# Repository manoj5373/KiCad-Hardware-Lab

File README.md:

# KiCad-Hardware-Lab
A collection of practical electronics and PCB design experiments developed using KiCad, covering analog circuits, digital logic, power supplies, counters, amplifiers, and hardware design.

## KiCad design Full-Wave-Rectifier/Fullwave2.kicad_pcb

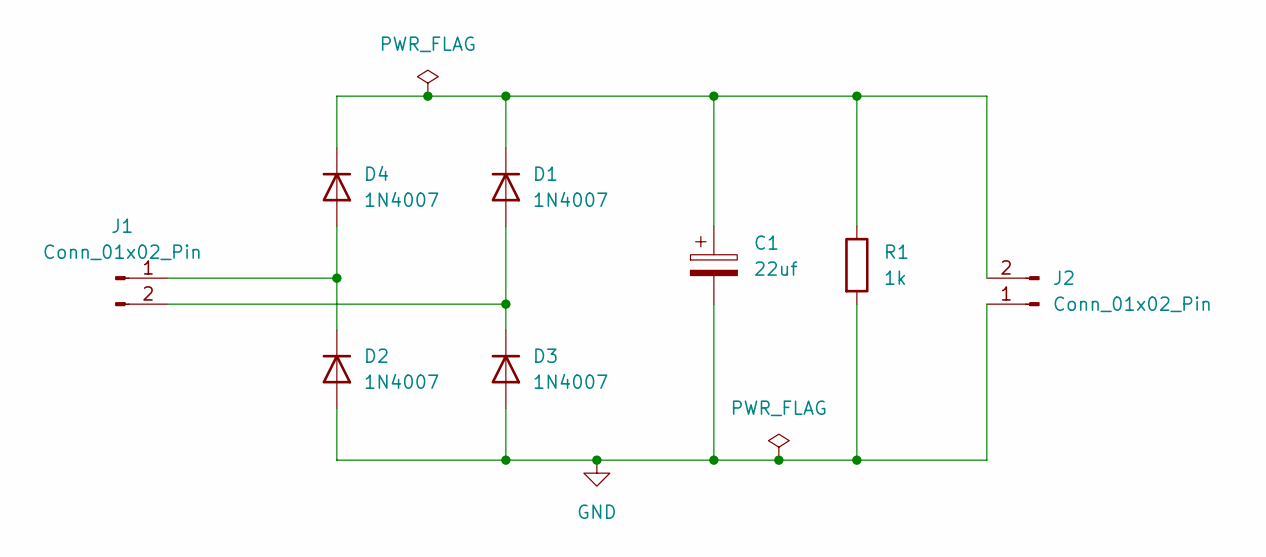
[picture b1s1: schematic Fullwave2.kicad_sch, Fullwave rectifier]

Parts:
C1: 22uf; CP_Radial_D6.3mm_P2.50mm
D1, D2, D3, D4: 1N4007; D_DO-41_SOD81_P10.16mm_Horizontal
J1, J2: Conn_01x02_Pin; PinHeader_1x02_P2.54mm_Vertical
R1: 1k; R_Axial_DIN0207_L6.3mm_D2.5mm_P10.16mm_Horizontal

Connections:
GND: C1.2, D2.2 (A), D3.2 (A), J2.1, R1.2
unnamed: D1.2 (A), D3.1 (K), J1.2
unnamed: C1.1, D1.1 (K), D4.1 (K), J2.2, R1.1
unnamed: D2.1 (K), D4.2 (A), J1.1

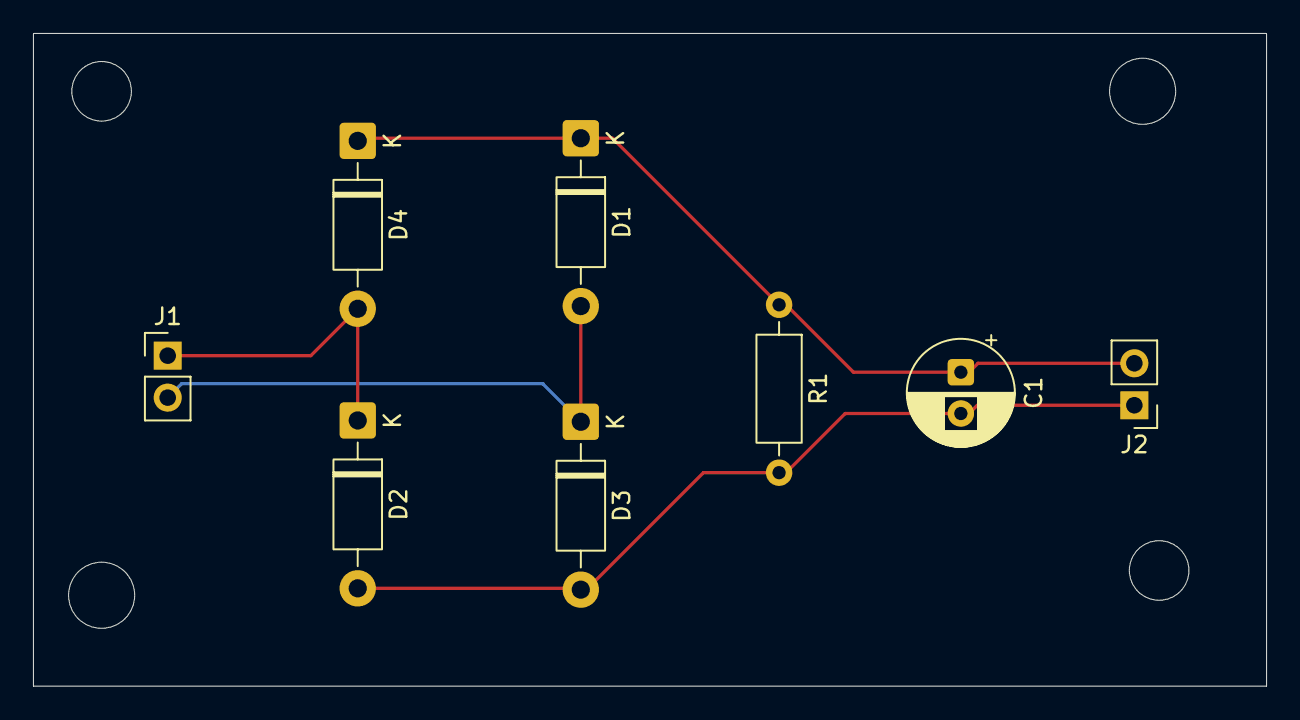
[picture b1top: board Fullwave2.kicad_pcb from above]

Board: 2 copper layers, 74.6 x 39.5 mm, 8 parts (0 on the bottom side), 4 nets.

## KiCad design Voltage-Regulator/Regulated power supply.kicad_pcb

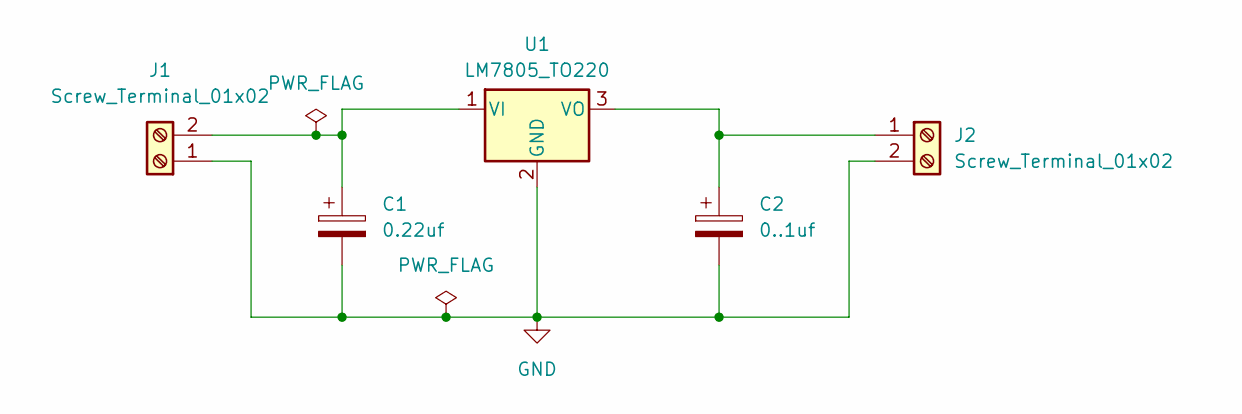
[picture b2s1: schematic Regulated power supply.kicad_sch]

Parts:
C1: 0.22uf; CP_Radial_D5.0mm_P2.50mm
C2: 0..1uf; CP_Radial_D5.0mm_P2.50mm
J1, J2: Screw_Terminal_01x02; TerminalBlock_Phoenix_PT-1,5-2-3.5-H_1x02_P3.50mm_Horizontal
U1: LM7805_TO220; TO-220-3_Vertical

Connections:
GND: C1.2, C2.2, J1.1, J2.2, U1.2 (GND)
unnamed: C1.1, J1.2, U1.1 (VI)
unnamed: C2.1, J2.1, U1.3 (VO)

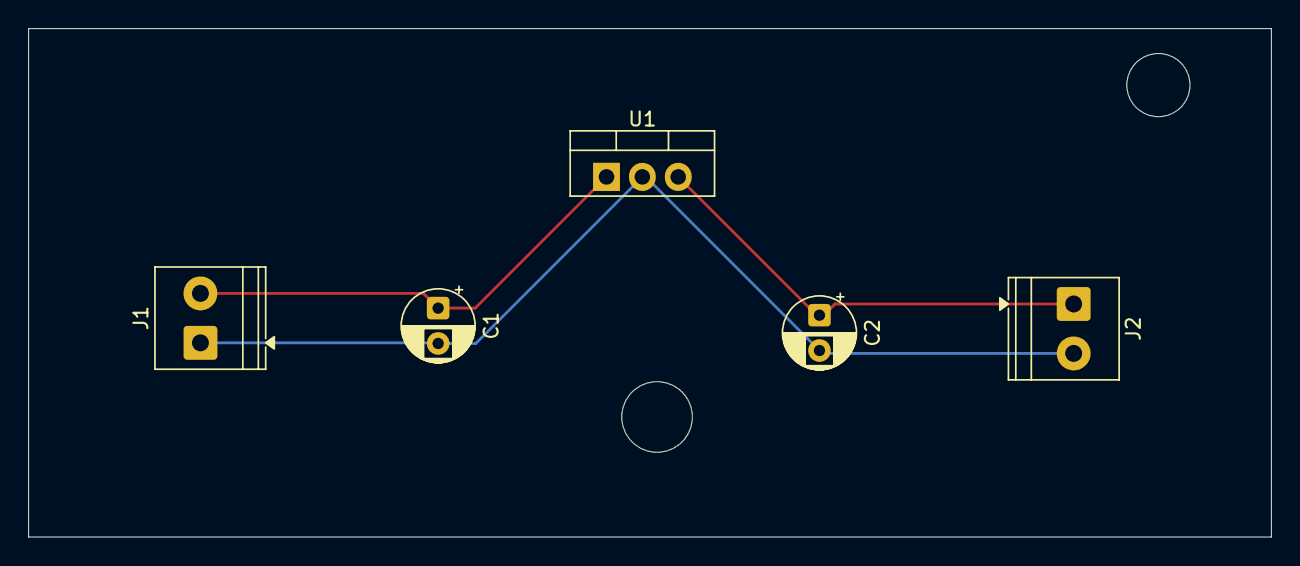
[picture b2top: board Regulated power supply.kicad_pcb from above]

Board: 2 copper layers, 88.0 x 36.0 mm, 5 parts (0 on the bottom side), 3 nets.

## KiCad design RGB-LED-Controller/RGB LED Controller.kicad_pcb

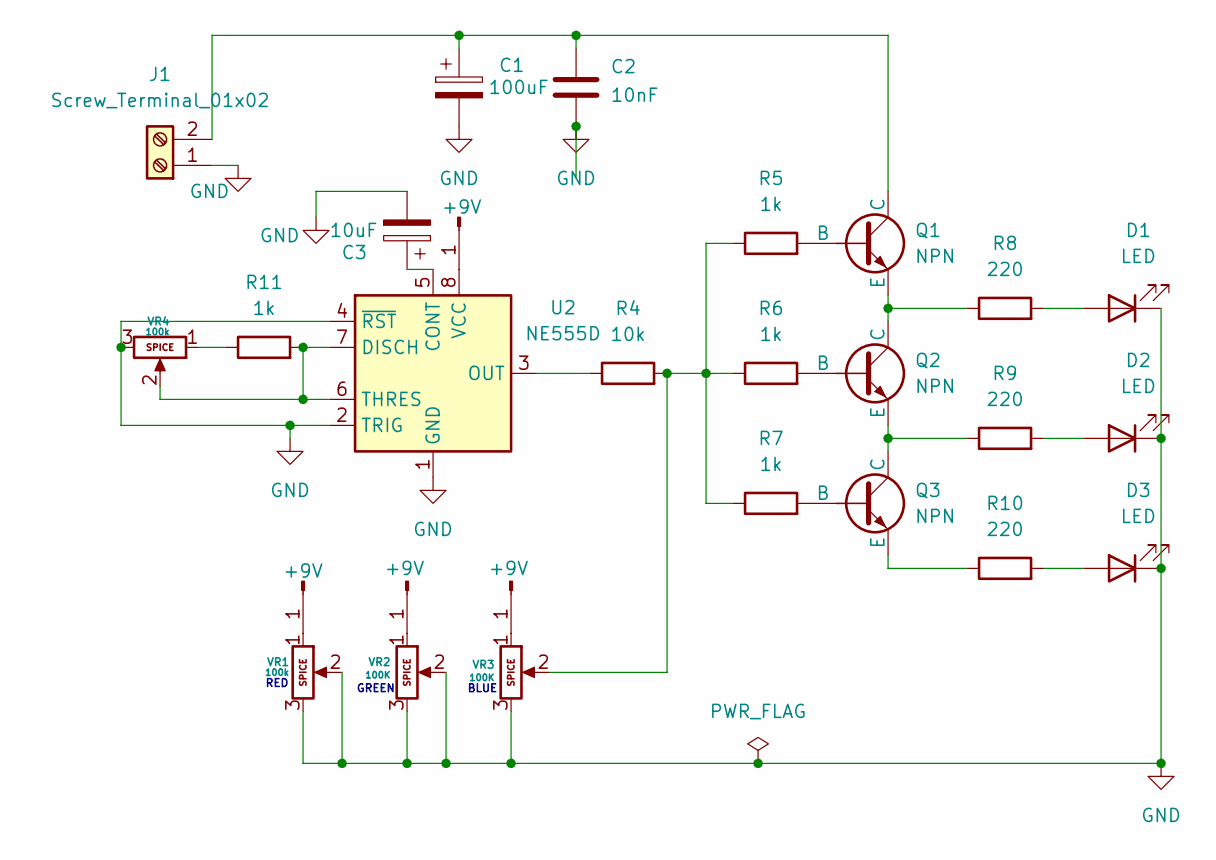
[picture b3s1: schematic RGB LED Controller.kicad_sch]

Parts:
C1: 100uF; CP_Radial_D5.0mm_P2.50mm
C2: 10nF; CP_Radial_D5.0mm_P2.50mm
C3: 10uF; CP_Radial_D5.0mm_P2.50mm
D1, D2, D3: LED; LED_D5.0mm
J1: Screw_Terminal_01x02; TerminalBlock_Phoenix_MKDS-1,5-2-5.08_1x02_P5.08mm_Horizont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
J2, J3, J4, J5: +9V; PinHeader_1x01_P2.54mm_Vertical
Q1, Q2, Q3: NPN; TO-18-3
R4: 10k; R_Axial_DIN0207_L6.3mm_D2.5mm_P7.62mm_Horizontal
R5, R6, R7, R11: 1k; R_Axial_DIN0207_L6.3mm_D2.5mm_P7.62mm_Horizontal
R8, R9, R10: 220; R_Axial_DIN0207_L6.3mm_D2.5mm_P7.62mm_Horizontal
U2: NE555D; SOIC-8_3.9x4.9mm_P1.27mm
VR1, VR2, VR3, VR4: Potentiometer; Potentiometer_Bourns_3296W_Vertical

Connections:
GND: C1.2, C2.2, C3.2, D1.1 (K), D2.1 (K), D3.1 (K), J1.1, U2.1 (GND), U2.2 (TRIG), U2.4 (~RST), VR1.2, VR1.3, VR2.2, VR2.3, VR3.3, VR4.3
unnamed: D1.2 (A), R8.2
unnamed: D2.2 (A), R9.2
unnamed: D3.2 (A), R10.2
unnamed: C1.1, C2.1, J1.2, Q1.1 (C)
unnamed: J2.1 (Pin_1_1), VR1.1
unnamed: J3.1 (Pin_1_1), VR2.1
unnamed: J4.1 (Pin_1_1), VR3.1
unnamed: J5.1 (Pin_1_1), U2.8 (VCC)
unnamed: Q1.2 (B), R5.2
unnamed: Q1.3 (E), Q2.1 (C), R8.1
unnamed: Q2.2 (B), R6.2
unnamed: Q2.3 (E), Q3.1 (C), R9.1
unnamed: Q3.2 (B), R7.2
unnamed: Q3.3 (E), R10.1
unnamed: R4.2, R5.1, R6.1, R7.1, VR3.2
unnamed: R11.1, VR4.1
unnamed: C3.1, U2.5 (CONT)
unnamed: R11.2, U2.6 (THRES), U2.7 (DISCH), VR4.2
unnamed: R4.1, U2.3 (OUT)

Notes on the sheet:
BLUE
RED
GREEN

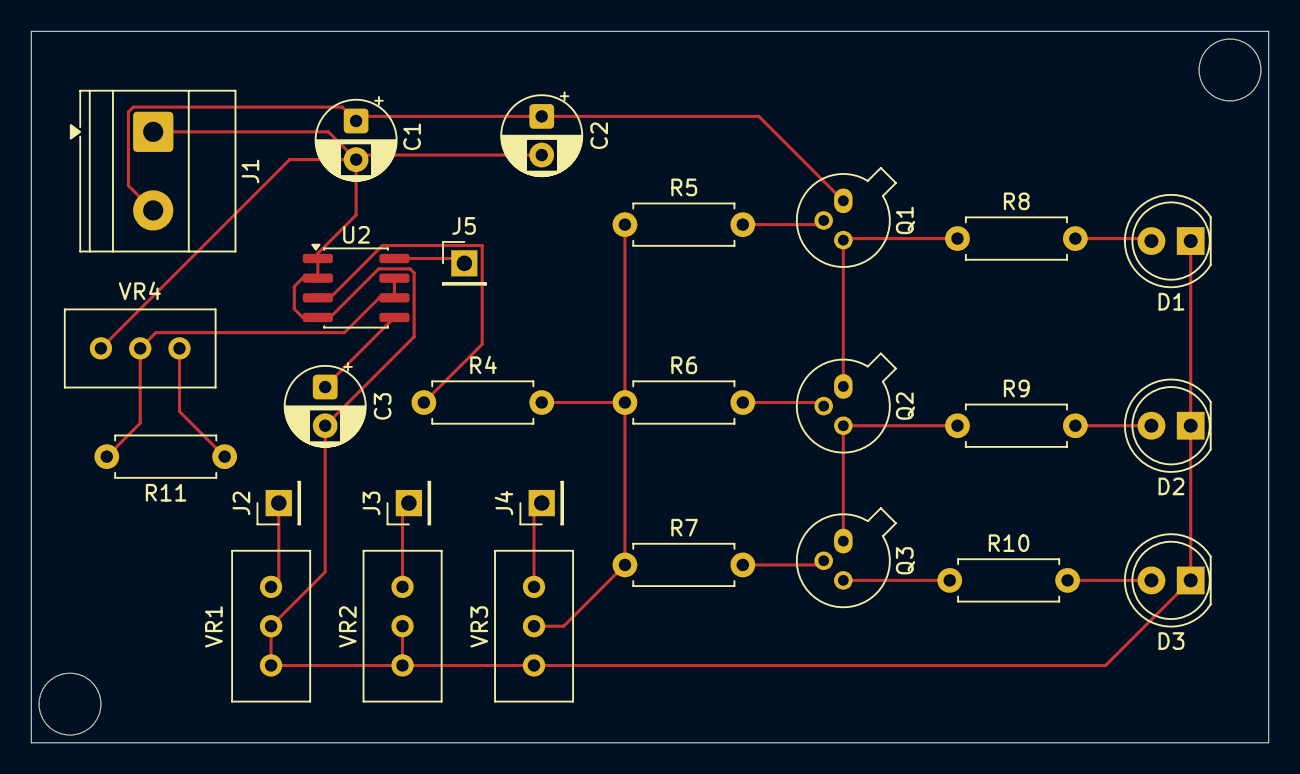
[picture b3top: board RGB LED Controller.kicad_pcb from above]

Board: 2 copper layers, 80.0 x 46.0 mm, 27 parts (0 on the bottom side), 20 nets.

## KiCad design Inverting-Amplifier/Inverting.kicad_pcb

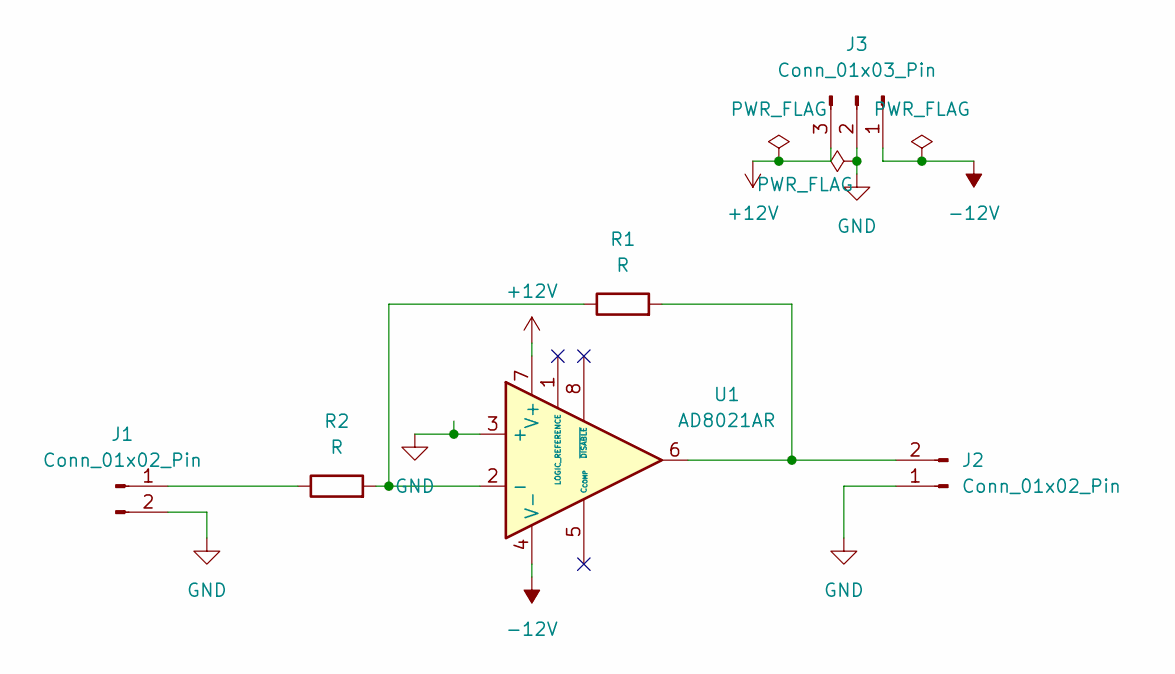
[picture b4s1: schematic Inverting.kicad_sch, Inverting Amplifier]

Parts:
J1, J2: Conn_01x02_Pin; Samtec_HPM-02-01-x-S_Straight_1x02_Pitch5.08mm
J3: Conn_01x03_Pin; Samtec_HPM-03-01-x-S_Straight_1x03_Pitch5.08mm
R1, R2: R; R_Axial_DIN0207_L6.3mm_D2.5mm_P10.16mm_Horizontal
U1: AD8021AR; SOIC-8_3.9x4.9mm_P1.27mm

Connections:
+12V: J3.3, U1.7 (V+)
-12V: J3.1, U1.4 (V-)
GND: J1.2, J2.1, J3.2, U1.3 (+)
unnamed: J1.1, R2.1
unnamed: J2.2, R1.2, U1.6
unnamed: R1.1, R2.2, U1.2 (-)

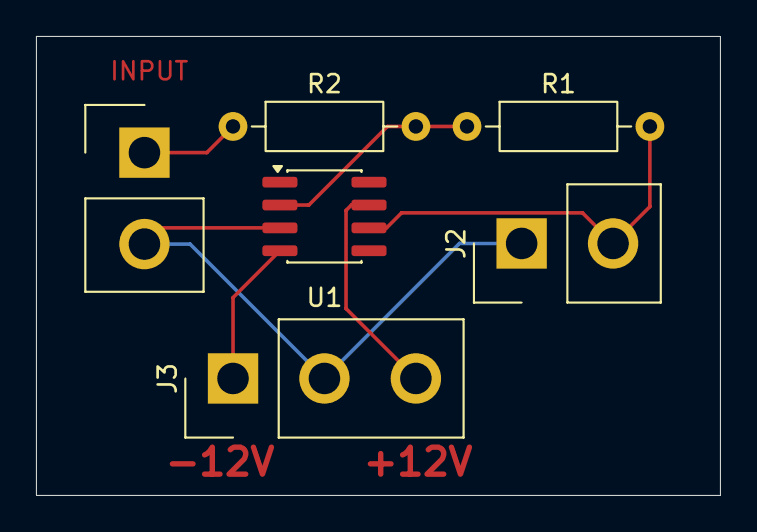
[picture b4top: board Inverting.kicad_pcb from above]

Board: 2 copper layers, 38.0 x 25.5 mm, 6 parts (0 on the bottom side), 6 nets.

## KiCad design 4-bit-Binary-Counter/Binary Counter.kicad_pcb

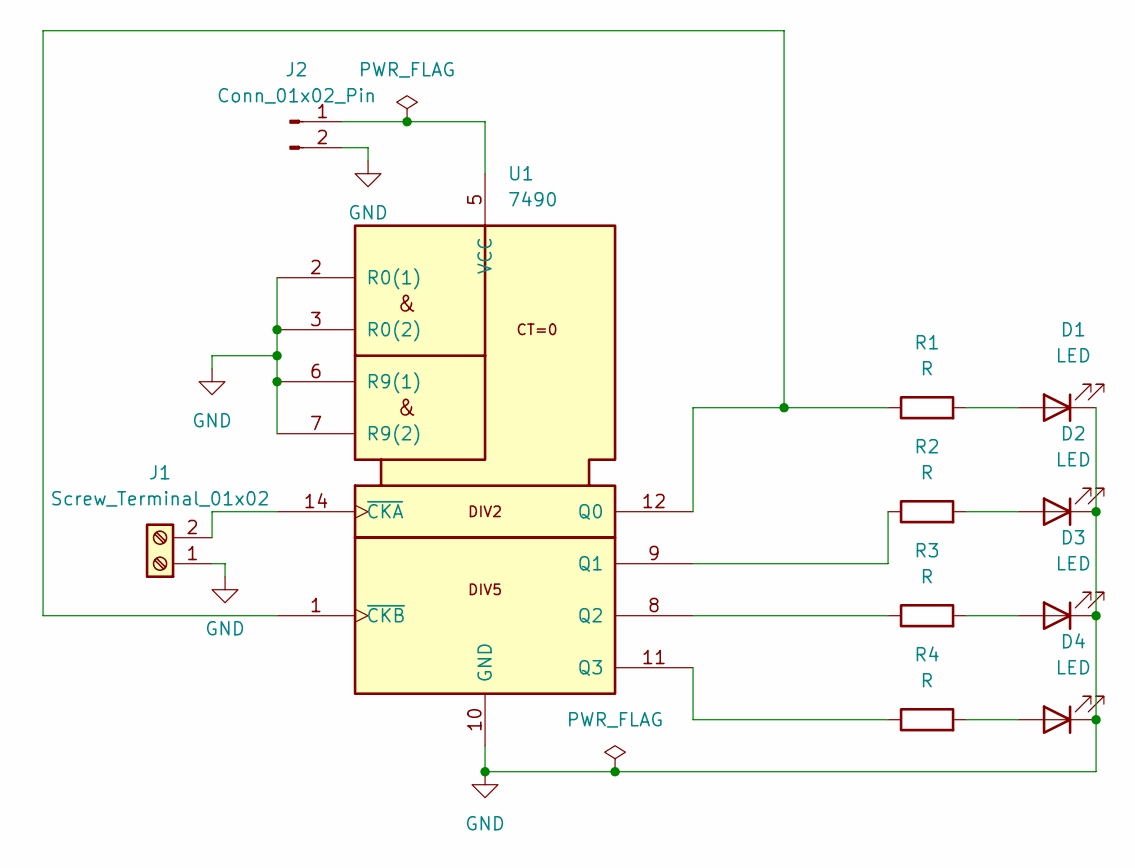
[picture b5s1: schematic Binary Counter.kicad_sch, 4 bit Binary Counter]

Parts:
D1, D2, D3, D4: LED; LED_D5.0mm
J1: Screw_Terminal_01x02; TerminalBlock_Phoenix_MKDS-1,5-2-5.08_1x02_P5.08mm_Horizont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
J2: Conn_01x02_Pin; PinHeader_1x02_P2.54mm_Vertical
R1, R2, R3, R4: R; R_Axial_DIN0207_L6.3mm_D2.5mm_P10.16mm_Horizontal
U1: 7490; DIP-14_W7.62mm

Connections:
GND: D1.1 (K), D2.1 (K), D3.1 (K), D4.1 (K), J1.1, J2.2, U1.2 (R0(1)), U1.3 (R0(2)), U1.6 (R9(1)), U1.7 (R9(2)), U1.10 (GND)
unnamed: D1.2 (A), R1.2
unnamed: D2.2 (A), R2.2
unnamed: D3.2 (A), R3.2
unnamed: D4.2 (A), R4.2
unnamed: J1.2, U1.14 (~CKA)
unnamed: J2.1, U1.5 (VCC)
unnamed: R1.1, U1.1 (~CKB), U1.12 (Q0)
unnamed: R2.1, U1.9 (Q1)
unnamed: R3.1, U1.8 (Q2)
unnamed: R4.1, U1.11 (Q3)

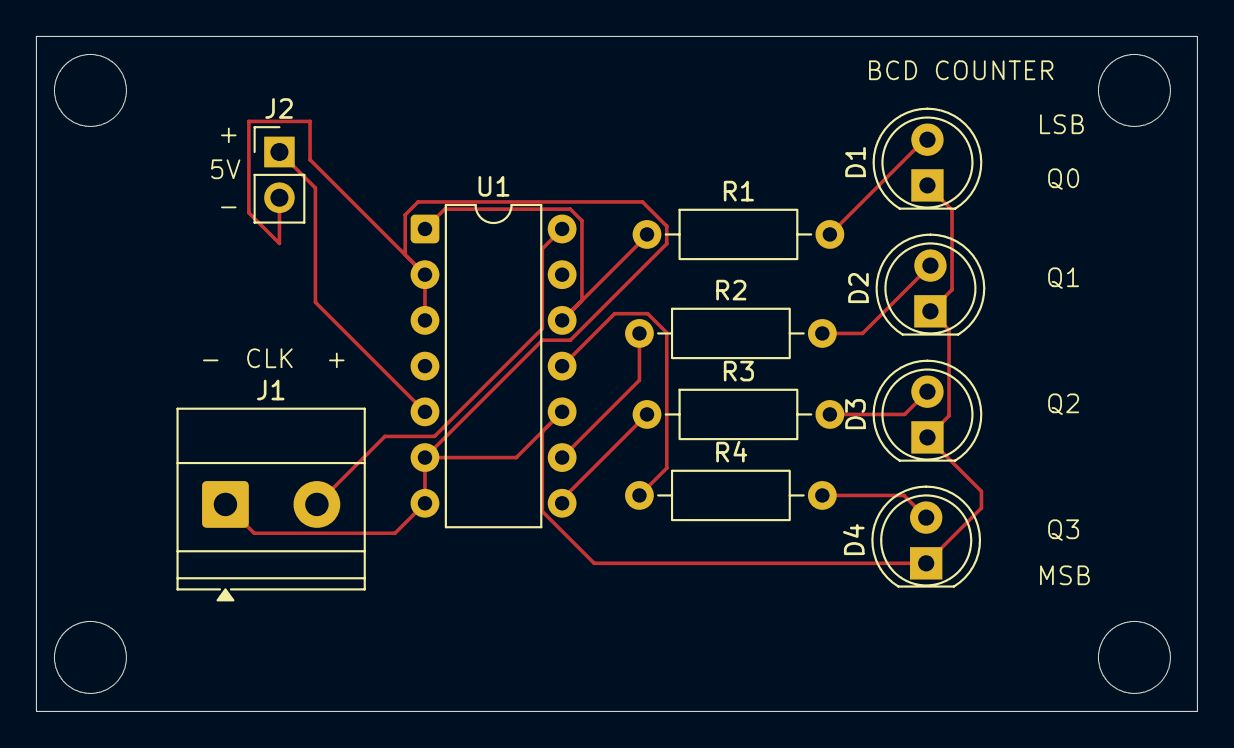
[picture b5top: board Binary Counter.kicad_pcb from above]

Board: 2 copper layers, 64.5 x 37.5 mm, 11 parts (0 on the bottom side), 11 nets.

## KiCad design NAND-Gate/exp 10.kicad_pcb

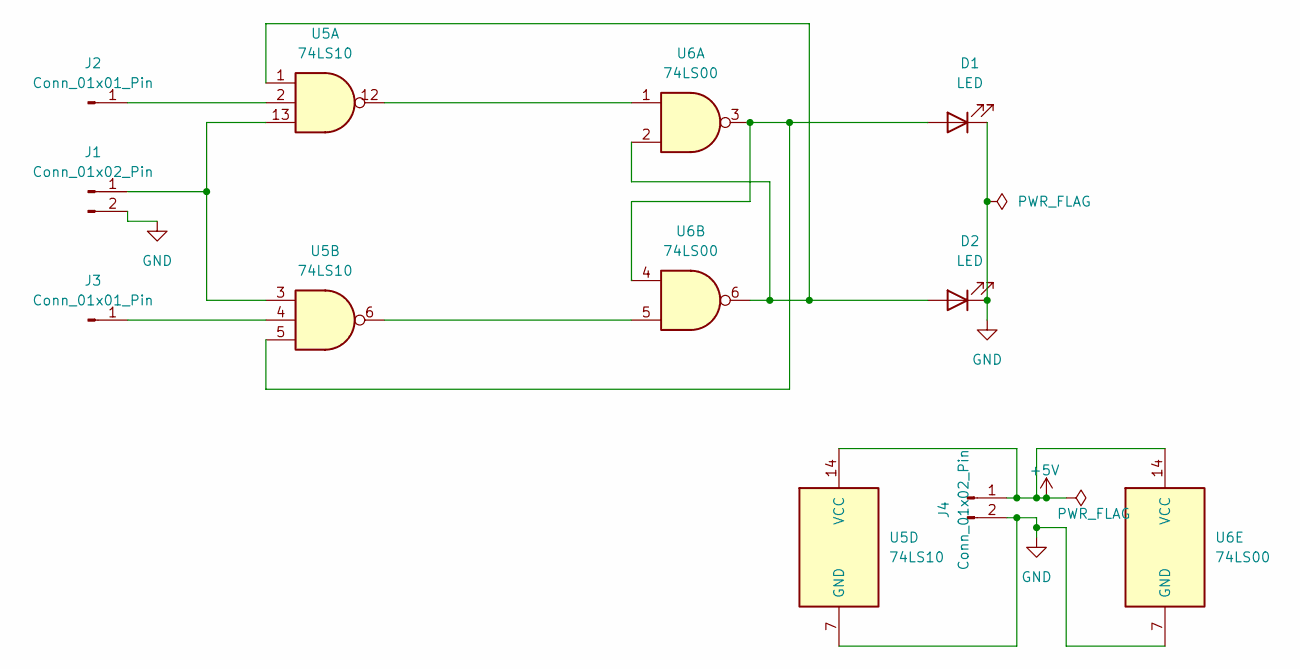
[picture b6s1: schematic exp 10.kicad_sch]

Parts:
D1, D2: LED; LED_D3.0mm
J1, J4: Conn_01x02_Pin; PinHeader_1x02_P2.54mm_Vertical
J2, J3: Conn_01x01_Pin; PinHeader_1x01_P2.54mm_Vertical
U5: 74LS10; DIP-14_W7.62mm
U6: 74LS00; DIP-14_W7.62mm

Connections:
+5V: J4.1, U5.14 (VCC), U6.14 (VCC)
GND: D1.1 (K), D2.1 (K), J1.2, J4.2, U5.7 (GND), U6.7 (GND)
unnamed: D1.2 (A), U5.5, U6.3, U6.4
unnamed: D2.2 (A), U5.1, U6.2, U6.6
unnamed: J1.1, U5.3, U5.13
unnamed: J2.1 (Pin_1_1), U5.2
unnamed: J3.1 (Pin_1_1), U5.4
unnamed: U5.6, U6.5
unnamed: U5.12, U6.1

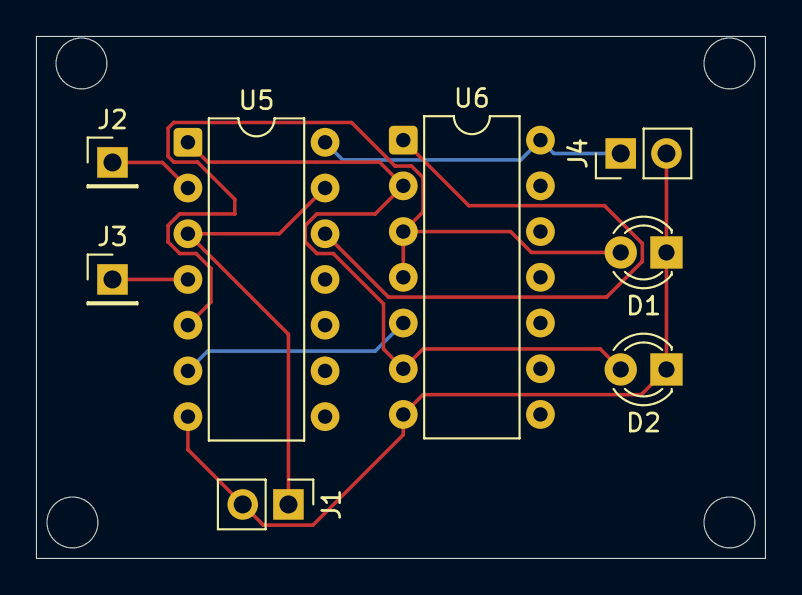
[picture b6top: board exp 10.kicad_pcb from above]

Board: 2 copper layers, 40.5 x 29.0 mm, 8 parts (0 on the bottom side), 9 nets.

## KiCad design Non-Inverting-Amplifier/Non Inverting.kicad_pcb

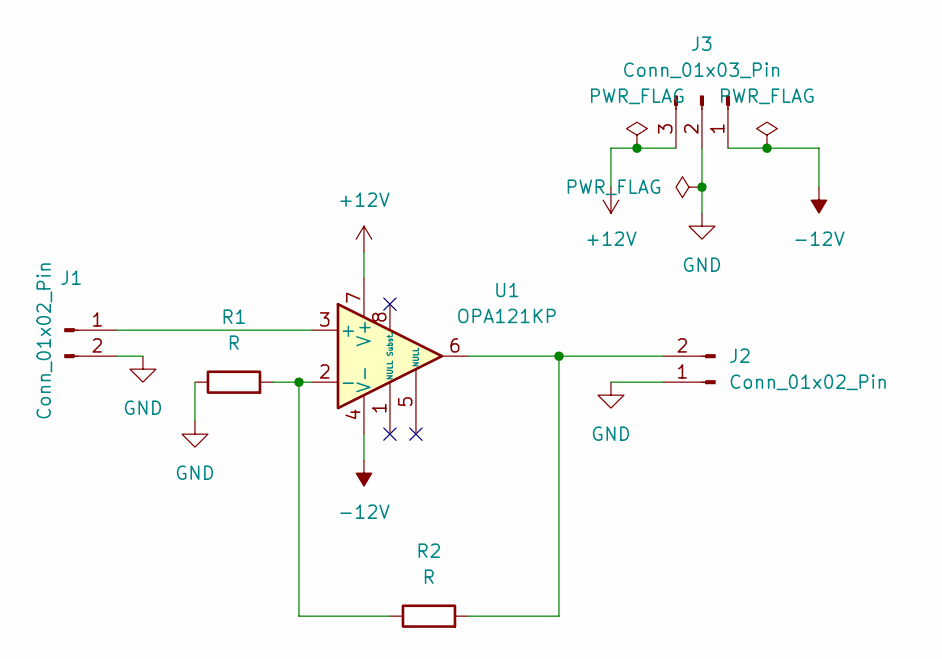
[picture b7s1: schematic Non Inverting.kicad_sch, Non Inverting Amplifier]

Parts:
J1, J2: Conn_01x02_Pin; Samtec_HPM-02-01-x-S_Straight_1x02_Pitch5.08mm
J3: Conn_01x03_Pin; Samtec_HPM-03-01-x-S_Straight_1x03_Pitch5.08mm
R1, R2: R; R_Axial_DIN0207_L6.3mm_D2.5mm_P10.16mm_Horizontal
U1: OPA121KP; DIP-8_W7.62mm

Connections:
+12V: J3.3, U1.7 (V+)
-12V: J3.1, U1.4 (V-)
GND: J1.2, J2.1, J3.2, R1.1
unnamed: J1.1, U1.3 (+)
unnamed: J2.2, R2.2, U1.6
unnamed: R1.2, R2.1, U1.2 (-)

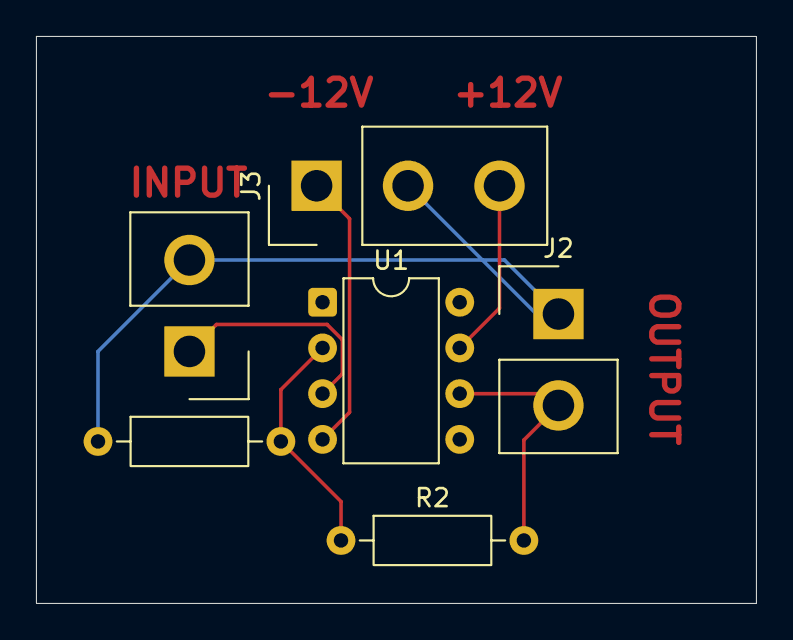
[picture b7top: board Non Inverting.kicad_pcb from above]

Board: 2 copper layers, 40.0 x 31.5 mm, 6 parts (0 on the bottom side), 6 nets.

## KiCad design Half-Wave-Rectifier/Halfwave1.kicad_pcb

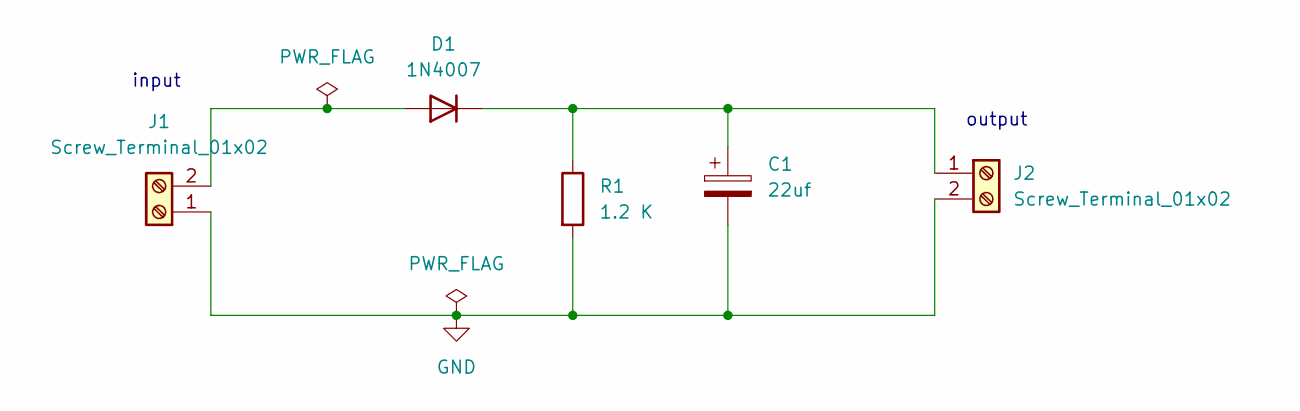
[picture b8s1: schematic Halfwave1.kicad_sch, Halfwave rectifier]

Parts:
C1: 22uf; CP_Radial_D5.0mm_P2.50mm
D1: 1N4007; D_DO-41_SOD81_P10.16mm_Horizontal
J1, J2: Screw_Terminal_01x02; TerminalBlock_Phoenix_PT-1,5-2-5.0-H_1x02_P5.00mm_Horizontal
R1: 1.2 K; R_Axial_DIN0207_L6.3mm_D2.5mm_P10.16mm_Horizontal

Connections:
GND: C1.2, J1.1, J2.2, R1.2
unnamed: D1.2 (A), J1.2
unnamed: C1.1, D1.1 (K), J2.1, R1.1

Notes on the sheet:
input
output

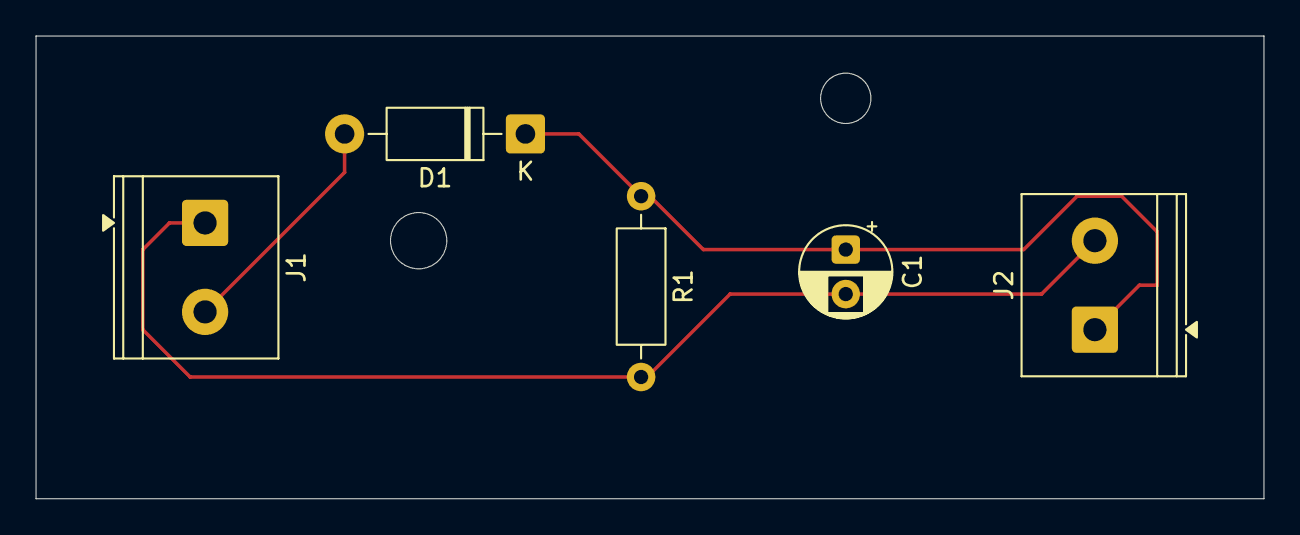
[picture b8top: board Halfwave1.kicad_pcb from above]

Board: 2 copper layers, 69.0 x 26.0 mm, 5 parts (0 on the bottom side), 3 nets.
